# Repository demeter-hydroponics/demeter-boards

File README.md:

# demeter-boards
This is where all the EE related files will go into

All the board data has been stored in these files. Updates will be made and pushed with commit messages
Calculations and other documents will remain on OneDrive

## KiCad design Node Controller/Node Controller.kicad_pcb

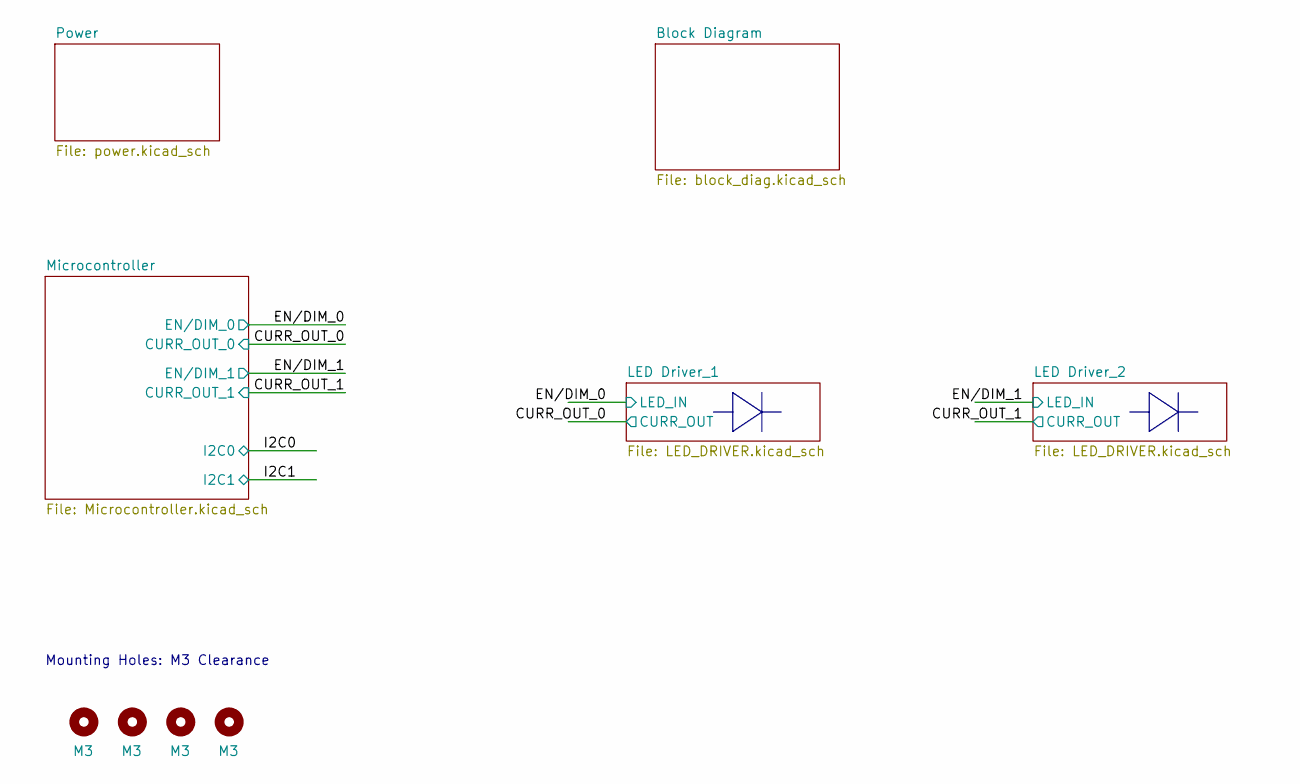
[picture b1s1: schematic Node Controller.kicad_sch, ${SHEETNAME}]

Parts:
H1, H2, H3, H4: M3; MountingHole_3.2mm_M3

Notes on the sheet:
Mounting Holes: M3 Clearance

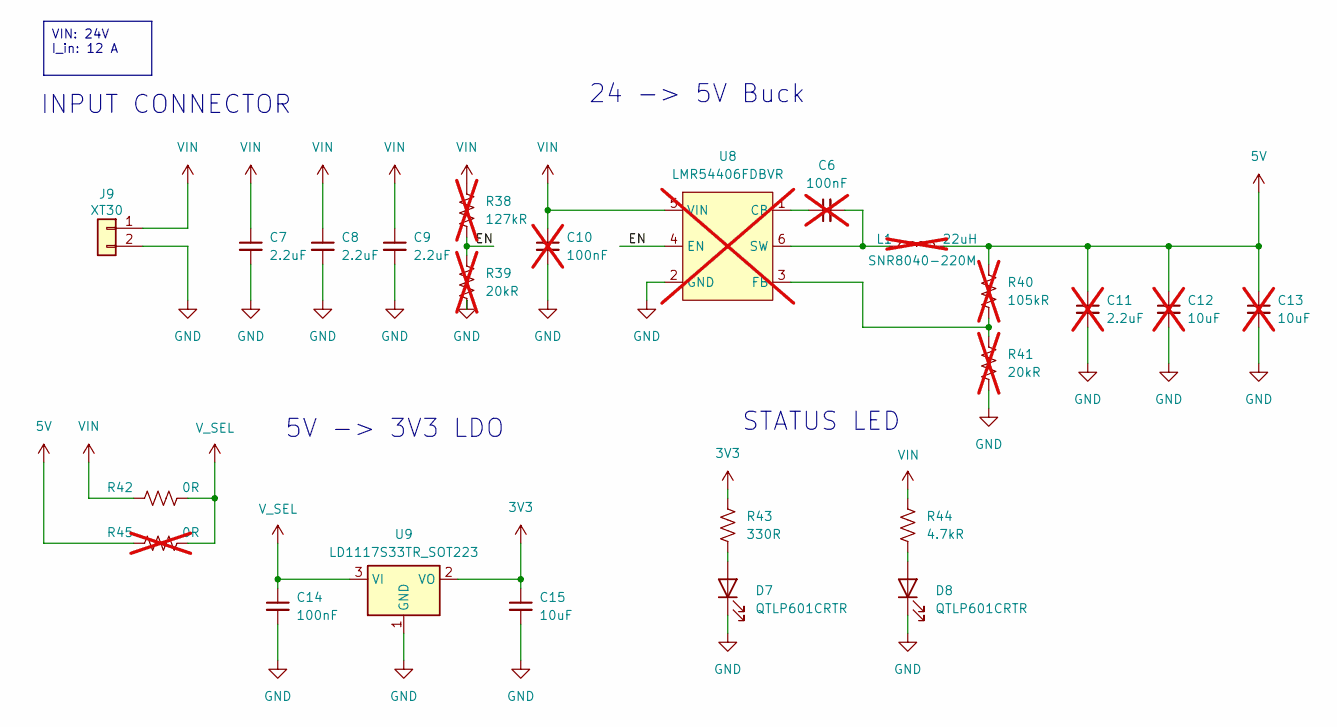
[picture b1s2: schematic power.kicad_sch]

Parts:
C6, C10: 100nF; C_1206_3216Metric; Part Number CL31B104KCFNNNE; not fitted
C7, C8, C9: 2.2uF; C_1206_3216Metric; Part Number CL31B225KCHSNNE
C11: 2.2uF; C_1206_3216Metric; Part Number CL31B225KCHSNNE; not fitted
C12, C13: 10uF; C_1210_3225Metric; Part Number CL32B106KMVNNWE; not fitted
C14: 100nF; C_1206_3216Metric; Part Number CL31B104KCFNNNE
C15: 10uF; C_1210_3225Metric; Part Number CL32B106KMVNNWE
D7, D8: QTLP601CRTR; LED_0603_1608Metric; Part Number QTLP601CRTR
J9: XT30; Part Number XT30
L1: 22uH; L_Bourns-SRN8040_8x8.15mm; Part Number SNR8040-220M; not fitted
R38: 127kR; R_0402_1005Metric; Part Number RC0603FR-07127KL; not fitted
R39, R41: 20kR; R_0402_1005Metric; Part Number RC0603FR-0720KL; not fitted
R40: 105kR; R_0402_1005Metric; Part Number RC0603FR-07105KL; not fitted
R42: 0R; R_0603_1608Metric; Part Number RC0603FR-070RL
R43: 330R; R_0402_1005Metric; Part Number RC0603FR-07330RL
R44: 4.7kR; R_0603_1608Metric; Part Number RC0603FR-074K7L
R45: 0R; R_0603_1608Metric; Part Number RC0603FR-070RL; not fitted
U8: LMR54406FDBVR; SOT-23-6; Part Number LMR54406FDBVR; not fitted
U9: LD1117S33TR_SOT223; SOT-223-3_TabPin2; Part Number LD1117S33TR_SOT223

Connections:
3V3: C15.1, R43.2, U9.2 (VO); also elsewhere on the board
5V: C11.1, C12.1, C13.1, L1.2, R40.1, R45.1; also elsewhere on the board
/Power/EN: R38.2, R39.1, U8.4 (EN)
GND: C7.2, C8.2, C9.2, C10.2, C11.2, C12.2, C13.2, C14.2, C15.2, D7.1 (K), D8.1 (K), J9.2, R39.2, R41.2, U8.2 (GND), U9.1 (GND); also elsewhere on the board
unnamed: D7.2 (A), R43.1
unnamed: D8.2 (A), R44.1
unnamed: C6.1, U8.1 (CB)
unnamed: R40.2, R41.1, U8.3 (FB)
unnamed: C6.2, L1.1, U8.6 (SW)
VIN: C7.1, C8.1, C9.1, C10.1, J9.1, R38.1, R42.1, R44.2, U8.5 (VIN)
V_SEL: C14.1, R42.2, R45.2, U9.3 (VI)

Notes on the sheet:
VIN: 24V I_in: 12 A
5V -> 3V3 LDO
STATUS LED
24 -> 5V Buck
INPUT CONNECTOR

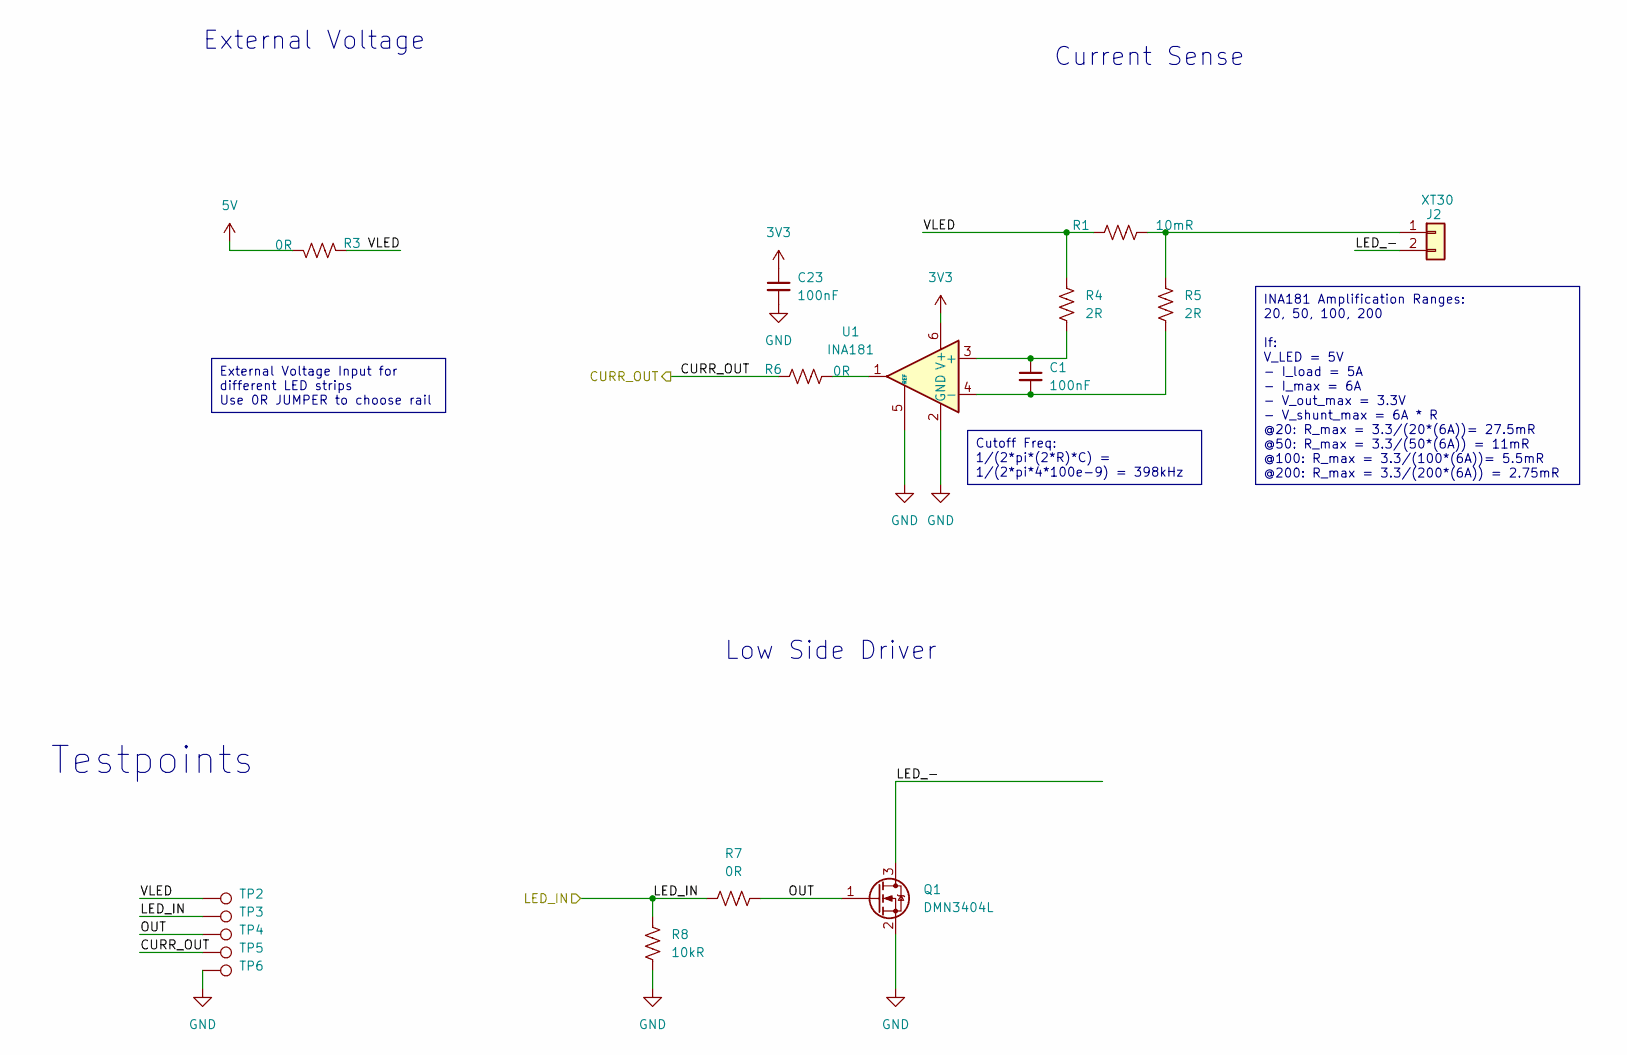
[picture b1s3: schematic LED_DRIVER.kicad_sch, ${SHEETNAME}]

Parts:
C1: 100nF; C_0603_1608Metric; Part Number CL31B104KCFNNNE
C23: 100nF; C_1206_3216Metric; Part Number CL31B104KCFNNNE
J2: XT30; Part Number XT30
Q1: DMN3404L; SOT-23; Part Number DMN3404L
R1: 10mR; R_0805_2012Metric; Part Number PA0805FRF870R01L
R3, R6, R7: 0R; R_0603_1608Metric; Part Number RC0603FR-070RL
R4, R5: 2R; R_0402_1005Metric; Part Number RC0402FR-072RL
R8: 10kR; R_0603_1608Metric; Part Number RC0603FR-0710KL
TP2, TP3, TP4, TP5, TP6: TestPoint_Pad_D1.0mm
U1: INA181; SOT-23-6; Part Number INA181A3IDBV

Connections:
3V3: C23.1, U1.6 (V+); also elsewhere on the board
5V: R3.1; also elsewhere on the board
/CURR_OUT_0: R6.2, TP5.1; also elsewhere on the board
/EN/DIM_0: R7.1, R8.2, TP3.1; also elsewhere on the board
/LED Driver_1/LED_-: J2.2, Q1.3 (D)
/LED Driver_1/OUT: Q1.1 (G), R7.2, TP4.1
/LED Driver_1/VLED: R1.1, R3.2, R4.2, TP2.1
GND: C23.2, Q1.2 (S), R8.1, TP6.1, U1.2 (GND), U1.5 (REF); also elsewhere on the board
unnamed: J2.1, R1.2, R5.2
unnamed: R6.1, U1.1
unnamed: C1.1, R4.1, U1.3 (+)
unnamed: C1.2, R5.1, U1.4 (-)

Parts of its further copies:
C5: 100nF; C_0603_1608Metric; Part Number CL31B104KCFNNNE
C24: 100nF; C_1206_3216Metric; Part Number CL31B104KCFNNNE
J8: XT30; Part Number XT30
Q7: DMN3404L; SOT-23; Part Number DMN3404L
R29: 10mR; R_0805_2012Metric; Part Number PA0805FRF870R01L
R31, R34, R35: 0R; R_0603_1608Metric; Part Number RC0603FR-070RL
R32, R33: 2R; R_0402_1005Metric; Part Number RC0402FR-072RL
R36: 10kR; R_0603_1608Metric; Part Number RC0603FR-0710KL
TP20, TP21, TP22, TP23, TP24: TestPoint_Pad_D1.0mm
U6: INA181; SOT-23-6; Part Number INA181A3IDBV

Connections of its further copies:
3V3: C24.1, U6.6 (V+); also elsewhere on the board
5V: R31.1; also elsewhere on the board
/CURR_OUT_1: R34.2, TP23.1; also elsewhere on the board
/EN/DIM_1: R35.1, R36.2, TP21.1; also elsewhere on the board
/LED Driver_2/LED_-: J8.2, Q7.3 (D)
/LED Driver_2/OUT: Q7.1 (G), R35.2, TP22.1
/LED Driver_2/VLED: R29.1, R31.2, R32.2, TP20.1
GND: C24.2, Q7.2 (S), R36.1, TP24.1, U6.2 (GND), U6.5 (REF); also elsewhere on the board
unnamed: J8.1, R29.2, R33.2
unnamed: R34.1, U6.1
unnamed: C5.1, R32.1, U6.3 (+)
unnamed: C5.2, R33.1, U6.4 (-)

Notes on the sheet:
Cutoff Freq: 1/(2*pi*(2*R)*C) = 1/(2*pi*4*100e-9) = 398kHz
INA181 Amplification Ranges: 20, 50, 100, 200 If: V_LED = 5V - I_load = 5A - I_max = 6A - V_out_max = 3.3V - V_shunt_max = 6A * R @20: R_max = 3.3/(20*(6A))= 27.5mR @50: R_max = 3.3/(50*(6A)) = 11mR @100: R_max = 3.3/(100*(6A))= 5.5mR @200: R_max = 3.3/(200*(6A)) = 2.75mR
External Voltage Input for different LED strips Use 0R JUMPER to choose rail
External Voltage
Testpoints
Low Side Driver
Current Sense

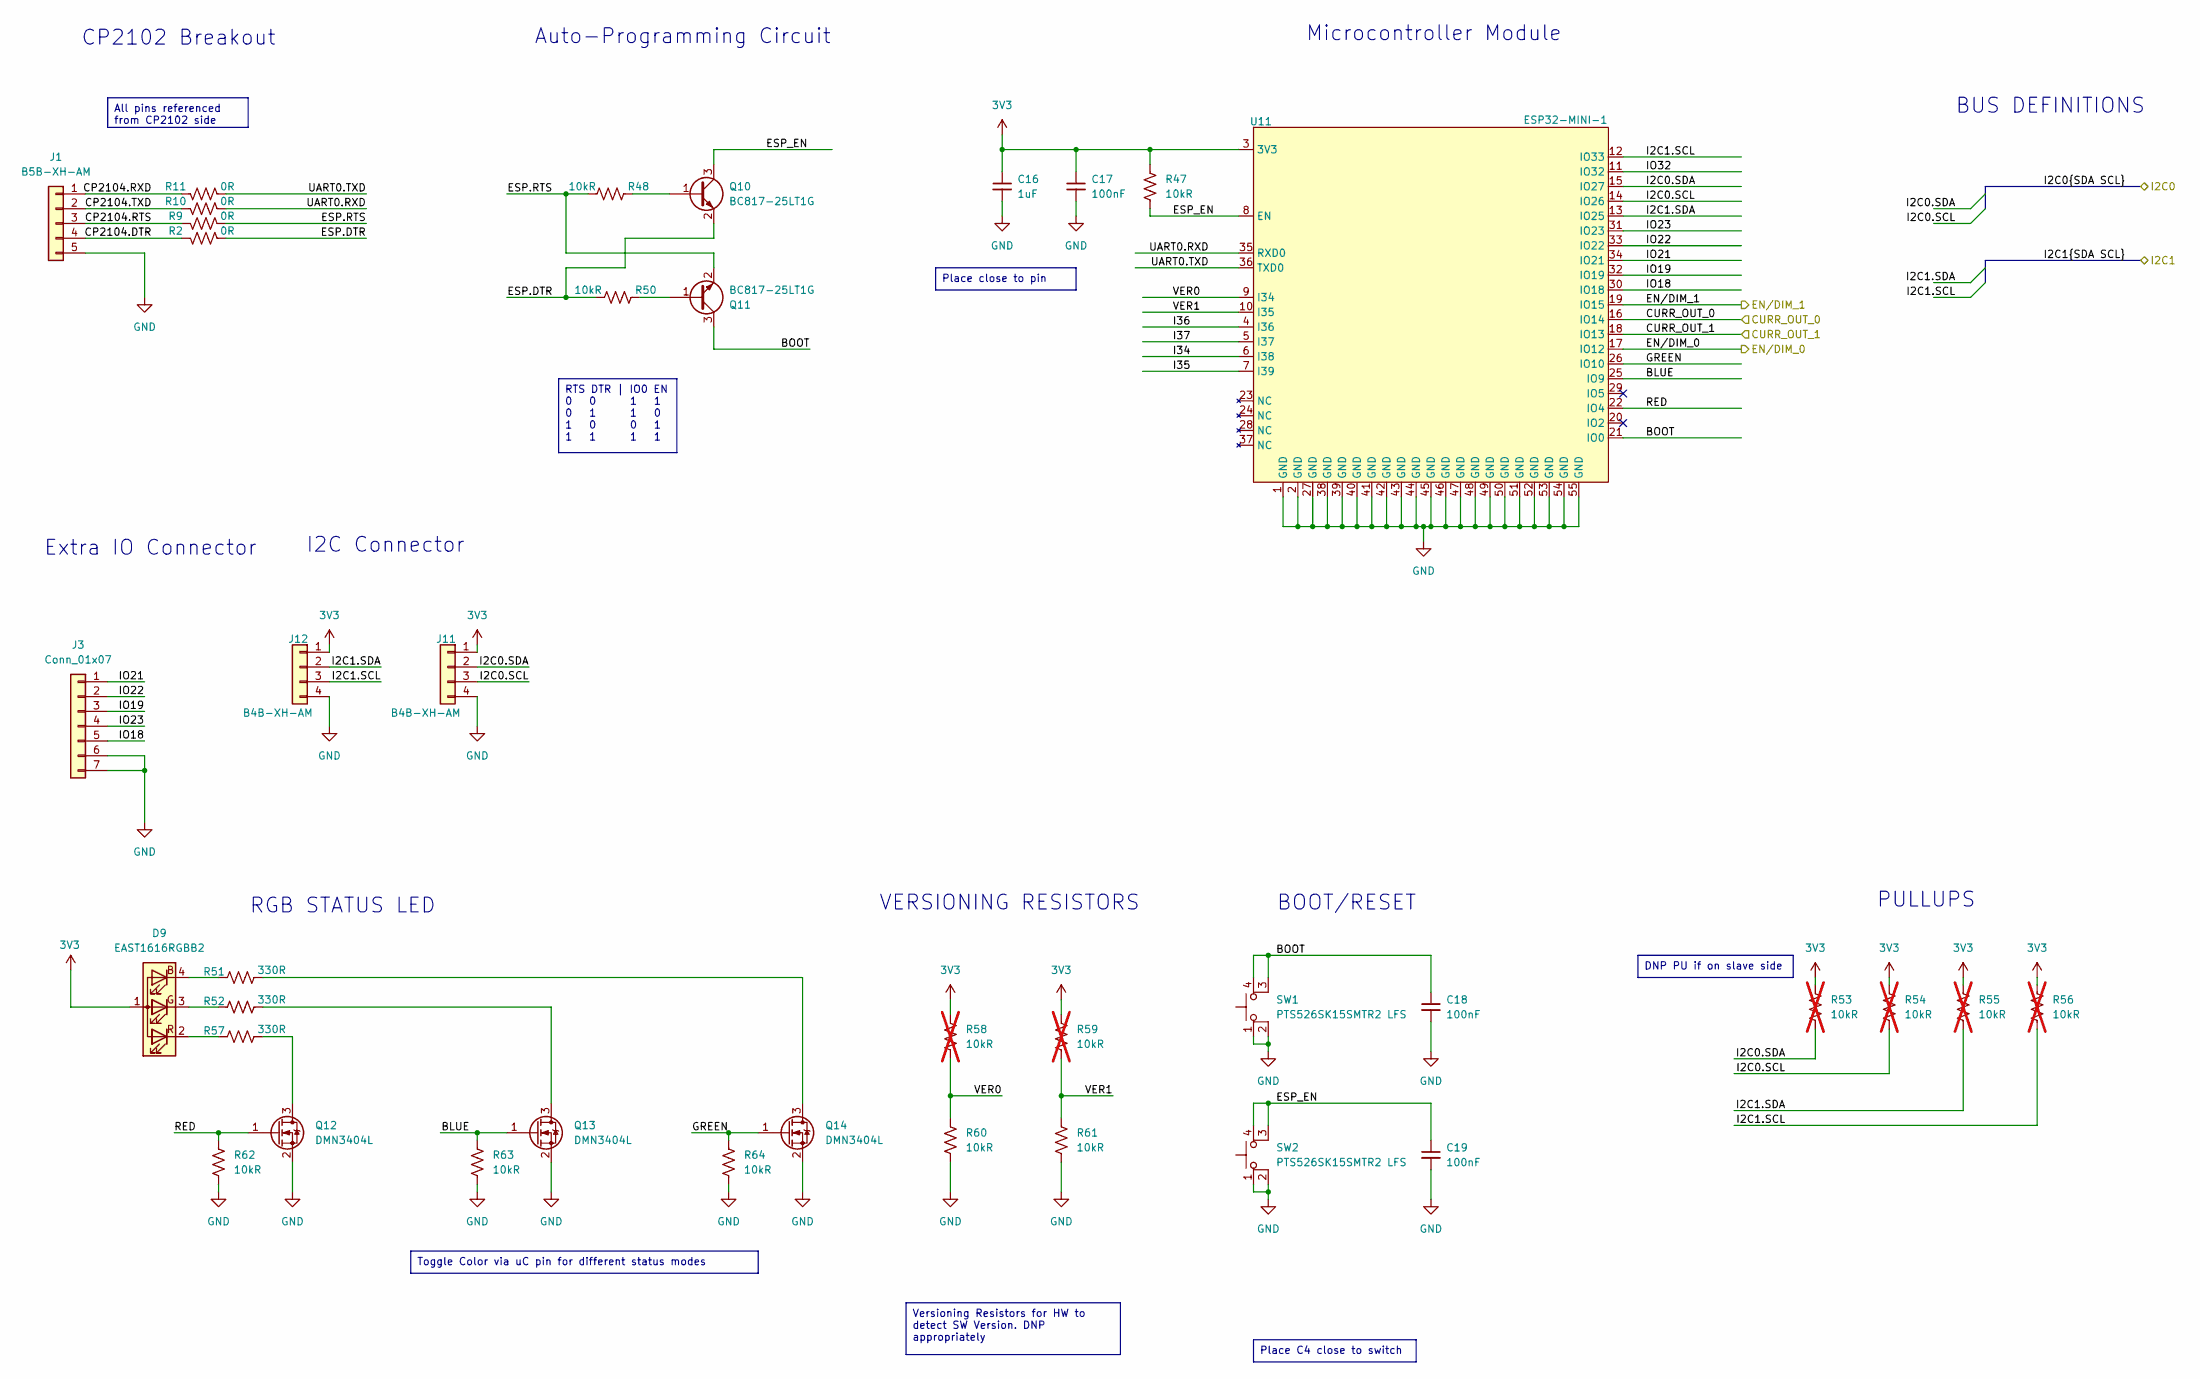
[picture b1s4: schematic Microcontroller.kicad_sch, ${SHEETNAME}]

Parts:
C16: 1uF; C_1206_3216Metric; Part Number CL31B105KCHNNNE
C17, C18, C19: 100nF; C_1206_3216Metric; Part Number CL31B104KCFNNNE
D9: EAST1616RGBB2; Part Number EAST1616RGBB2
J1: B5B-XH-AM; JST_XH_B5B-XH-AM_1x05_P2.50mm_Vertical
J3: Conn_01x07; PinSocket_1x07_P2.54mm_Vertical
J11, J12: B4B-XH-AM; JST_XH_B4B-XH-AM_1x04_P2.50mm_Vertical; Part Number B4B-XH-AM
Q10, Q11: BC817-25LT1G; SOT-23; Part Number BC817-25LT1G
Q12, Q13, Q14: DMN3404L; SOT-23; Part Number DMN3404L
R2, R9, R10, R11: 0R; R_0603_1608Metric; Part Number RC0603FR-070RL
R47, R48, R50, R60, R61, R62, R63, R64: 10kR; R_0603_1608Metric; Part Number RC0603FR-0710KL
R51, R52, R57: 330R; R_0402_1005Metric; Part Number RC0603FR-07330RL
R53, R54, R55, R56, R58, R59: 10kR; R_0603_1608Metric; Part Number RC0603FR-0710KL; not fitted
SW1, SW2: PTS526SK15SMTR2 LFS; Part Number PTS526SK15SMTR2 LFS
U11: ESP32-MINI-1

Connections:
3V3: C16.1, C17.1, D9.1 (A), J11.1, J12.1, R47.1, R53.1, R54.1, R55.1, R56.1, R58.1, R59.1, U11.3 (3V3); also elsewhere on the board
/CURR_OUT_0: U11.16 (IO14); also elsewhere on the board
/CURR_OUT_1: U11.18 (IO13); also elsewhere on the board
/EN/DIM_0: U11.17 (IO12); also elsewhere on the board
/EN/DIM_1: U11.19 (IO15); also elsewhere on the board
/Microcontroller/BLUE: Q13.1 (G), R63.1, U11.25 (IO9)
/Microcontroller/BOOT: C18.1, Q11.3 (C), SW1.3 (K), SW1.4 (A), U11.21 (IO0)
/Microcontroller/CP2104.DTR: J1.4, R2.2
/Microcontroller/CP2104.RTS: J1.3, R9.2
/Microcontroller/CP2104.RXD: J1.1, R11.2
/Microcontroller/CP2104.TXD: J1.2, R10.2
/Microcontroller/ESP.DTR: Q10.2 (E), R2.1, R50.1
/Microcontroller/ESP.RTS: Q11.2 (E), R9.1, R48.1
/Microcontroller/ESP_EN: C19.1, Q10.3 (C), R47.2, SW2.3 (K), SW2.4 (A), U11.8 (EN)
/Microcontroller/GREEN: Q14.1 (G), R64.1, U11.26 (IO10)
/Microcontroller/I2C0.SCL: J11.3, R54.2, U11.14 (IO26)
/Microcontroller/I2C0.SDA: J11.2, R53.2, U11.15 (IO27)
/Microcontroller/I2C1.SCL: J12.3, R56.2, U11.12 (IO33)
/Microcontroller/I2C1.SDA: J12.2, R55.2, U11.13 (IO25)
/Microcontroller/I34: U11.6 (I38)
/Microcontroller/I35: U11.7 (I39)
/Microcontroller/I36: U11.4 (I36)
/Microcontroller/I37: U11.5 (I37)
/Microcontroller/IO18: J3.5, U11.30 (IO18)
/Microcontroller/IO19: J3.3, U11.32 (IO19)
/Microcontroller/IO21: J3.1, U11.34 (IO21)
/Microcontroller/IO22: J3.2, U11.33 (IO22)
/Microcontroller/IO23: J3.4, U11.31 (IO23)
/Microcontroller/IO32: U11.11 (IO32)
/Microcontroller/RED: Q12.1 (G), R62.1, U11.22 (IO4)
/Microcontroller/UART0.RXD: R10.1, U11.35 (RXD0)
/Microcontroller/UART0.TXD: R11.1, U11.36 (TXD0)
/Microcontroller/VER0: R58.2, R60.1, U11.9 (I34)
/Microcontroller/VER1: R59.2, R61.1, U11.10 (I35)
GND: C16.2, C17.2, C18.2, C19.2, J1.5, J3.6, J3.7, J11.4, J12.4, Q12.2 (S), Q13.2 (S), Q14.2 (S), R60.2, R61.2, R62.2, R63.2, R64.2, SW1.1, SW1.2, SW2.1, SW2.2, U11.1 (GND), U11.2 (GND), U11.27 (GND), U11.38 (GND), U11.39 (GND), U11.40 (GND), U11.41 (GND), U11.42 (GND), U11.43 (GND), U11.44 (GND), U11.45 (GND), U11.46 (GND), U11.47 (GND), U11.48 (GND), U11.49 (GND), U11.50 (GND), U11.51 (GND), U11.52 (GND), U11.53 (GND), U11.54 (GND), U11.55 (GND); also elsewhere on the board
unnamed: D9.4 (BK), R51.1
unnamed: D9.3 (GK), R52.1
unnamed: D9.2 (RK), R57.1
unnamed: Q10.1 (B), R48.2
unnamed: Q11.1 (B), R50.2
unnamed: Q12.3 (D), R57.2
unnamed: Q13.3 (D), R52.2
unnamed: Q14.3 (D), R51.2

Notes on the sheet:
Place close to pin
Place C4 close to switch
Versioning Resistors for HW to detect SW Version. DNP appropriately
All pins referenced from CP2102 side
RTS DTR | IO0 EN 0 0 1 1 0 1 1 0 1 0 0 1 1 1 1 1
DNP PU if on slave side
Toggle Color via uC pin for different status modes
Auto-Programming Circuit
I2C Connector
CP2102 Breakout
Extra IO Connector
RGB STATUS LED
VERSIONING RESISTORS
Microcontroller Module
BOOT/RESET
PULLUPS
BUS DEFINITIONS

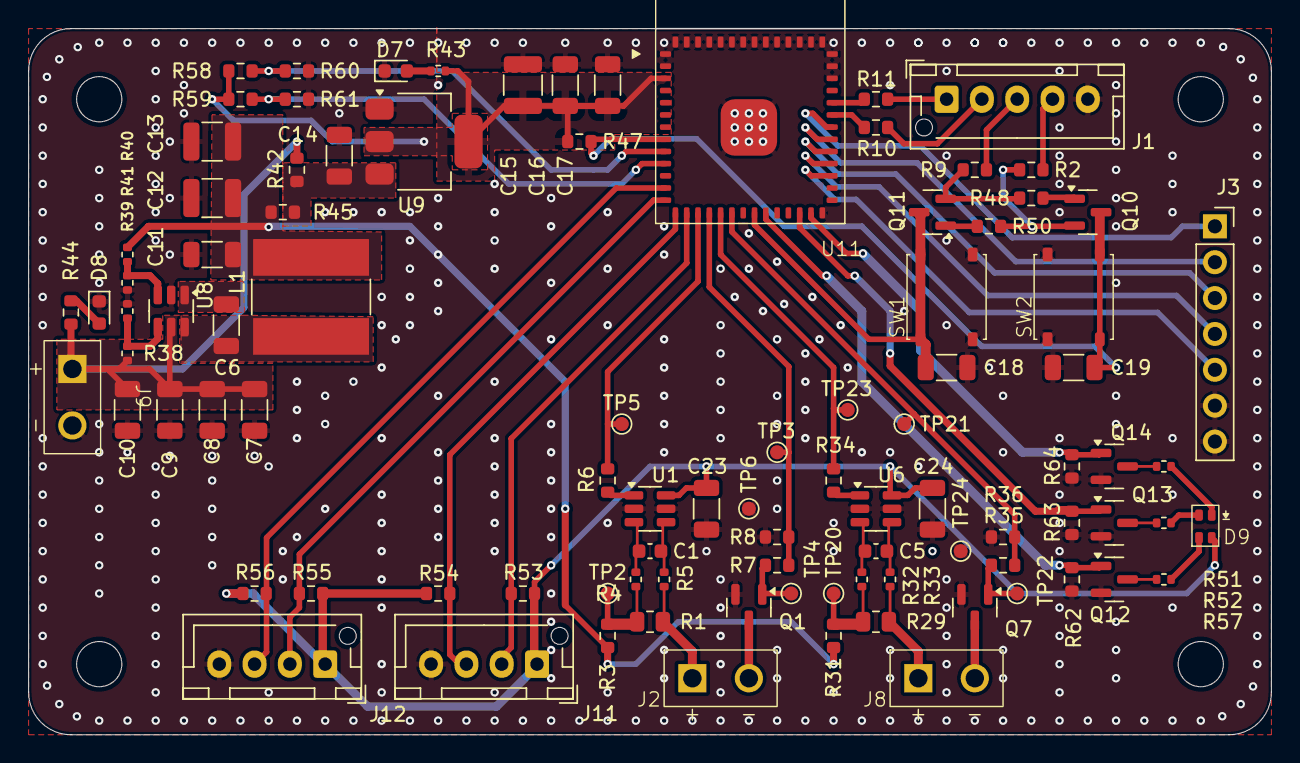
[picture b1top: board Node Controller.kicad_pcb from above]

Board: 4 copper layers, 88.0 x 50.0 mm, 100 parts (0 on the bottom side), 61 nets.

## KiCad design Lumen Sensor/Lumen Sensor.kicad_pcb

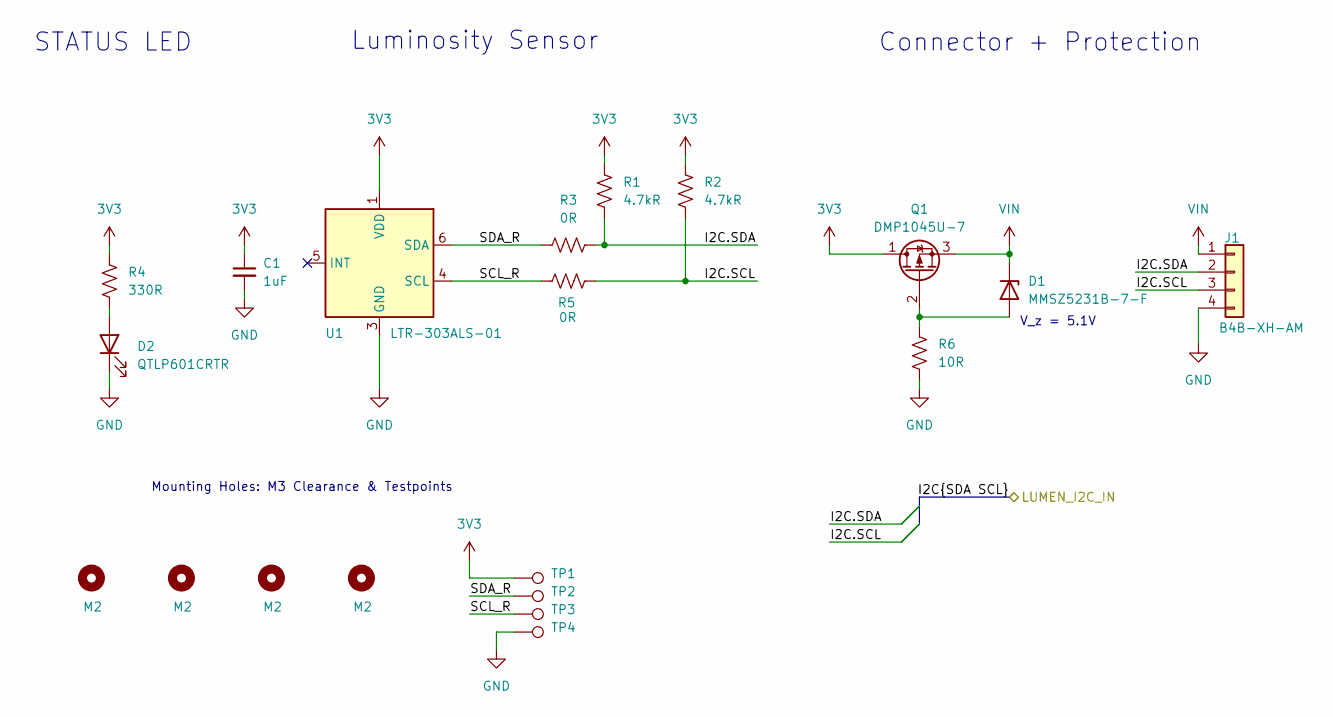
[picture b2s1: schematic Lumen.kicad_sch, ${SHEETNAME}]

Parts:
C1: 1uF; C_1206_3216Metric; Part Number CL31B105KCHNNNE
D1: MMSZ5231B-7-F; D_SOD-123; Part Number MMSZ5231B-7-F
D2: QTLP601CRTR; LED_0603_1608Metric; Part Number QTLP601CRTR
H1, H2, H3, H4: M2; MountingHole_2.2mm_M2_Pad
J1: B4B-XH-AM; JST_XH_B4B-XH-AM_1x04_P2.50mm_Vertical; Part Number B4B-XH-AM
Q1: DMP1045U-7; SOT-23-3; Part Number DMP1045U-7
R1, R2: 4.7kR; R_0603_1608Metric; Part Number RC0603FR-074K7L
R3, R5: 0R; R_0603_1608Metric; Part Number RC0603FR-070RL
R4: 330R; R_0402_1005Metric; Part Number RC0603FR-07330RL
R6: 10R; R_0402_1005Metric; Part Number RC0603FR-0710RL
TP1, TP2, TP3, TP4: TestPoint_Pad_D1.0mm
U1: LTR-303ALS-01; Lite-On_LTR-303ALS-01; Part Number LTR-303ALS-01

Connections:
3V3: C1.1, Q1.1 (D), R1.2, R2.2, R4.2, TP1.1, U1.1 (VDD)
/Lumen Board/I2C.SCL: J1.3, R2.1, R5.2
/Lumen Board/I2C.SDA: J1.2, R1.1, R3.2
/Lumen Board/SCL_R: R5.1, TP3.1, U1.4 (SCL)
/Lumen Board/SDA_R: R3.1, TP2.1, U1.6 (SDA)
GND: C1.2, D2.1 (K), J1.4, R6.2, TP4.1, U1.3 (GND)
unnamed: D1.2 (A), Q1.2 (G), R6.1
unnamed: D2.2 (A), R4.1
VIN: D1.1 (K), J1.1, Q1.3 (S)

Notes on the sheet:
Connector + Protection
V_z = 5.1V
STATUS LED
Luminosity Sensor
Mounting Holes: M3 Clearance & Testpoints

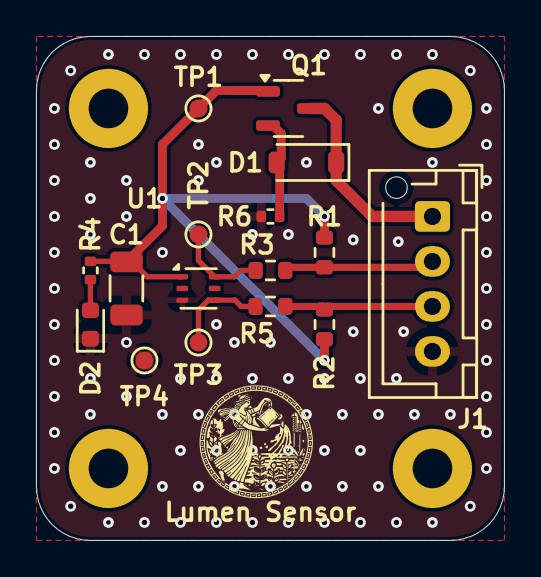
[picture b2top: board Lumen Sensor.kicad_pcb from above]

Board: 4 copper layers, 26.0 x 28.0 mm, 20 parts (0 on the bottom side), 9 nets.

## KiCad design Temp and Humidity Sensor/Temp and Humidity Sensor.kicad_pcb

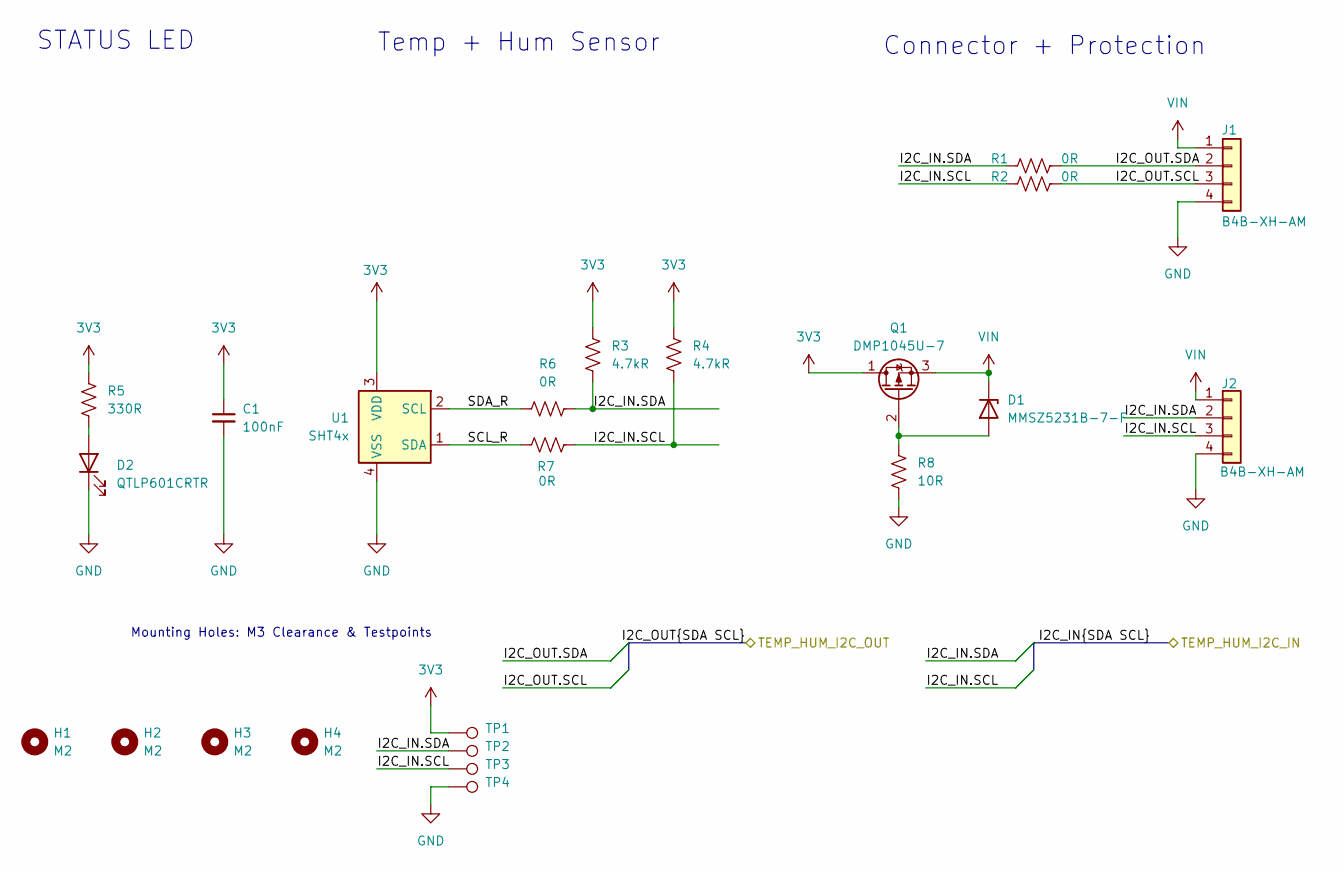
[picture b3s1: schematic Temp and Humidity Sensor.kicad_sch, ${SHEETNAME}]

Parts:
C1: 100nF; C_1206_3216Metric; Part Number CL31B104KCFNNNE
D1: MMSZ5231B-7-F; D_SOD-123; Part Number MMSZ5231B-7-F
D2: QTLP601CRTR; LED_0603_1608Metric; Part Number QTLP601CRTR
H1, H2, H3, H4: M2; MountingHole_2.2mm_M2_Pad
J1, J2: B4B-XH-AM; JST_XH_B4B-XH-AM_1x04_P2.50mm_Vertical; Part Number B4B-XH-AM
Q1: DMP1045U-7; SOT-23-3; Part Number DMP1045U-7
R1, R2, R6, R7: 0R; R_0603_1608Metric; Part Number RC0603FR-070RL
R3, R4: 4.7kR; R_0603_1608Metric; Part Number RC0603FR-074K7L
R5: 330R; R_0402_1005Metric; Part Number RC0603FR-07330RL
R8: 10R; R_0402_1005Metric; Part Number RC0603FR-0710RL
TP1, TP2, TP3, TP4: TestPoint_Pad_D1.0mm
U1: SHT4x; Sensirion_DFN-4_1.5x1.5mm_P0.8mm_SHT4x_NoCentralPad; Part Number SHT40-AD1B

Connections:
3V3: C1.1, Q1.1 (D), R3.2, R4.2, R5.2, TP1.1, U1.3 (VDD)
/I2C_IN.SCL: J2.3, R2.1, R4.1, R7.2, TP3.1
/I2C_IN.SDA: J2.2, R1.1, R3.1, R6.2, TP2.1
/I2C_OUT.SCL: J1.3, R2.2
/I2C_OUT.SDA: J1.2, R1.2
/SCL_R: R7.1, U1.1 (SDA)
/SDA_R: R6.1, U1.2 (SCL)
GND: C1.2, D2.1 (K), J1.4, J2.4, R8.2, TP4.1, U1.4 (VSS)
unnamed: D1.2 (A), Q1.2 (G), R8.1
unnamed: D2.2 (A), R5.1
VIN: D1.1 (K), J1.1, J2.1, Q1.3 (S)

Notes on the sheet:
Connector + Protection
Mounting Holes: M3 Clearance & Testpoints
Temp + Hum Sensor
STATUS LED

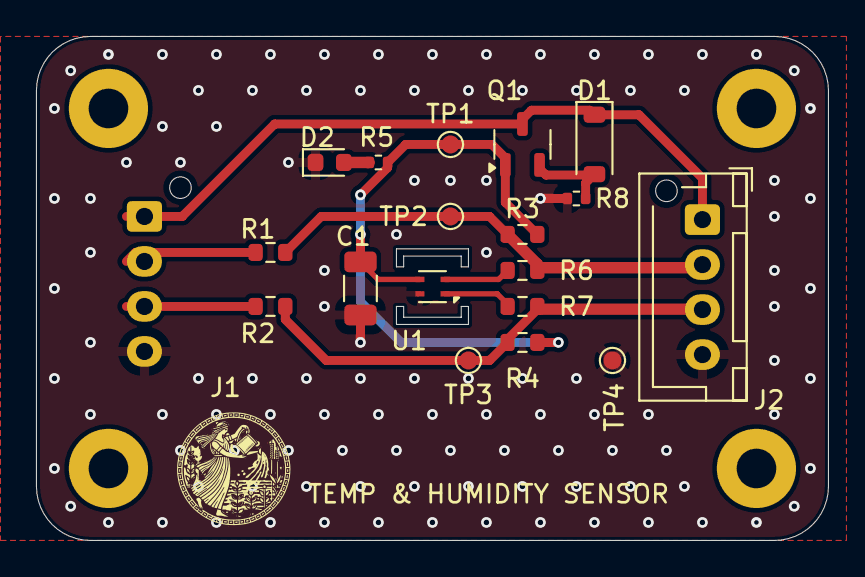
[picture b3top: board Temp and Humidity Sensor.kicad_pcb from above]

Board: 4 copper layers, 44.0 x 28.0 mm, 23 parts (1 on the bottom side), 11 nets.

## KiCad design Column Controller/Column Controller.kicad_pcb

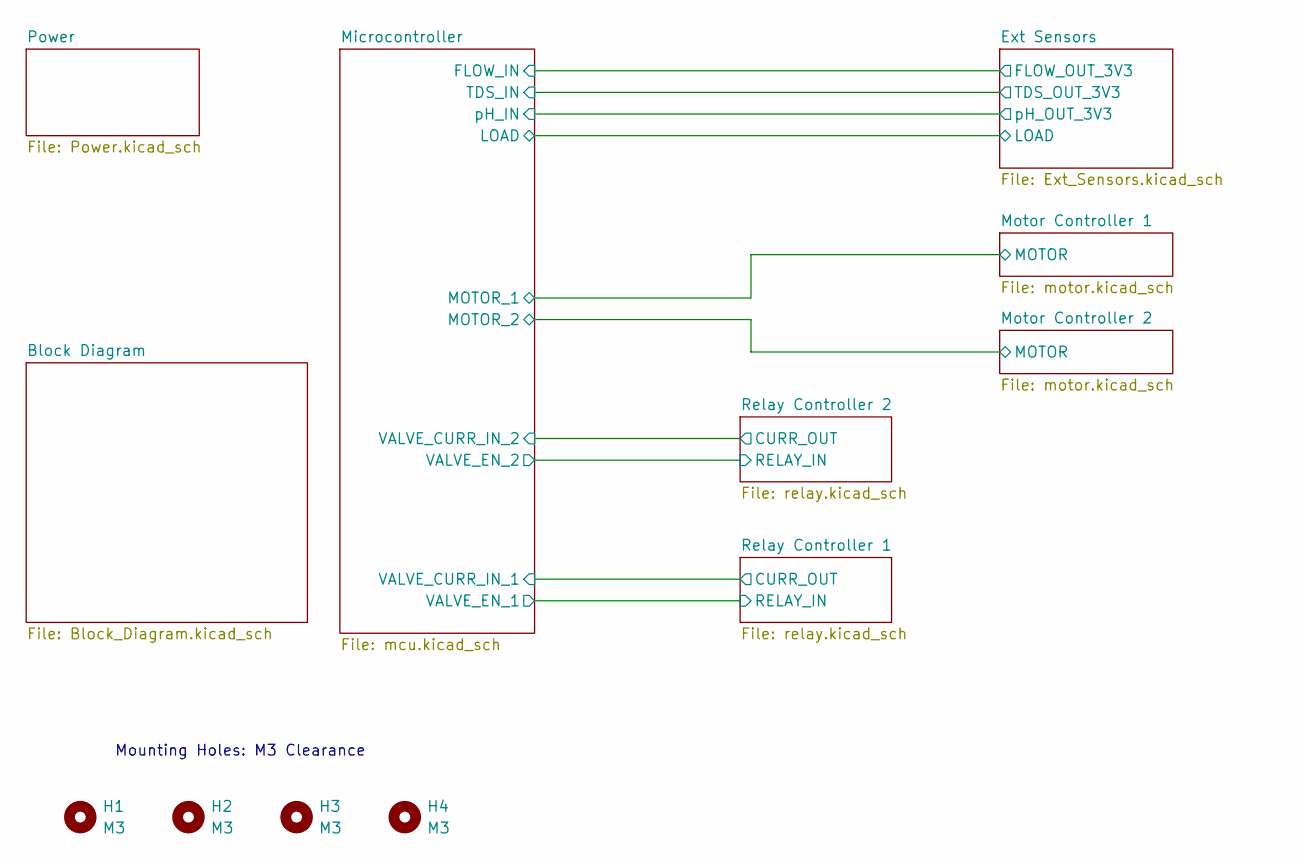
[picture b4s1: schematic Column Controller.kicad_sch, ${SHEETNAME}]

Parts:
H1, H2, H3, H4: M3; MountingHole_3.2mm_M3

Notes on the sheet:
Mounting Holes: M3 Clearance

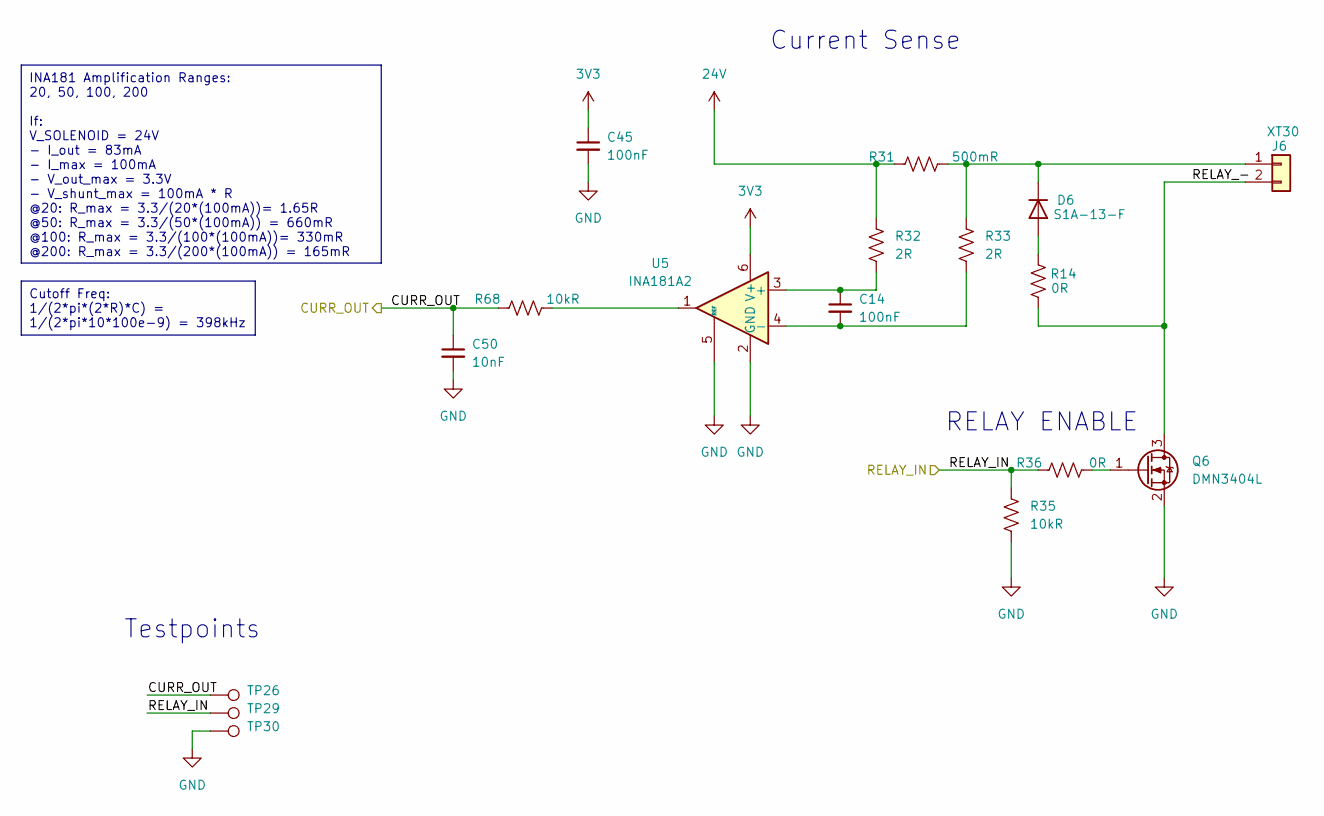
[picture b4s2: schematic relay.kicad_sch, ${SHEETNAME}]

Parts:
C14, C45: 100nF; C_0402_1005Metric; Part Number CL31B104KCFNNNE
C50: 10nF; C_0402_1005Metric; Part Number CL05B103KO5NNNC
D6: S1A-13-F; D_SMA
J6: XT30
Q6: DMN3404L; SOT-23; Part Number DMN3404L
R14, R36: 0R; R_0603_1608Metric; Part Number RC0603FR-070RL
R31: 500mR; R_0603_1608Metric; Part Number RL0603FR-070R5L
R32, R33: 2R; R_0402_1005Metric; Part Number RC0402FR-072RL
R35, R68: 10kR; R_0603_1608Metric; Part Number RC0603FR-0710KL
TP26, TP29, TP30: TestPoint_Pad_D1.0mm
U5: INA181A2; SOT-23-6; Part Number INA181A2IDVB

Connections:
3V3: C45.1, U5.6 (V+); also elsewhere on the board
24V: R31.1, R32.2; also elsewhere on the board
/Relay Controller 1/CURR_OUT: C50.1, R68.1, TP26.1; also elsewhere on the board
/Relay Controller 1/RELAY_-: J6.2, Q6.3 (D), R14.2
/Relay Controller 1/RELAY_IN: R35.2, R36.2, TP29.1; also elsewhere on the board
GND: C45.2, C50.2, Q6.2 (S), R35.1, TP30.1, U5.2 (GND), U5.5 (REF); also elsewhere on the board
unnamed: Q6.1 (G), R36.1
unnamed: R68.2, U5.1
unnamed: C14.1, R32.1, U5.3 (+)
unnamed: C14.2, R33.1, U5.4 (-)

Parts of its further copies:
C33, C47: 100nF; C_0402_1005Metric; Part Number CL31B104KCFNNNE
C51: 10nF; C_0402_1005Metric; Part Number CL05B103KO5NNNC
D4: S1A-13-F; D_SMA
J10: XT30
Q9: DMN3404L; SOT-23; Part Number DMN3404L
R16, R66: 0R; R_0603_1608Metric; Part Number RC0603FR-070RL
R62: 500mR; R_0603_1608Metric; Part Number RL0603FR-070R5L
R63, R64: 2R; R_0402_1005Metric; Part Number RC0402FR-072RL
R67, R69: 10kR; R_0603_1608Metric; Part Number RC0603FR-0710KL
TP27, TP34, TP35: TestPoint_Pad_D1.0mm
U11: INA181A2; SOT-23-6; Part Number INA181A2IDVB

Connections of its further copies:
3V3: C47.1, U11.6 (V+); also elsewhere on the board
24V: R62.1, R63.2; also elsewhere on the board
/Relay Controller 2/CURR_OUT: C51.1, R69.1, TP27.1; also elsewhere on the board
/Relay Controller 2/RELAY_-: J10.2, Q9.3 (D), R16.2
/Relay Controller 2/RELAY_IN: R66.2, R67.2, TP34.1; also elsewhere on the board
GND: C47.2, C51.2, Q9.2 (S), R67.1, TP35.1, U11.2 (GND), U11.5 (REF); also elsewhere on the board
unnamed: Q9.1 (G), R66.1
unnamed: R69.2, U11.1
unnamed: C33.1, R63.1, U11.3 (+)
unnamed: C33.2, R64.1, U11.4 (-)

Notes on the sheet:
INA181 Amplification Ranges: 20, 50, 100, 200 If: V_SOLENOID = 24V - I_out = 83mA - I_max = 100mA - V_out_max = 3.3V - V_shunt_max = 100mA * R @20: R_max = 3.3/(20*(100mA))= 1.65R @50: R_max = 3.3/(50*(100mA)) = 660mR @100: R_max = 3.3/(100*(100mA))= 330mR @200: R_max = 3.3/(200*(100mA)) = 165mR
Cutoff Freq: 1/(2*pi*(2*R)*C) = 1/(2*pi*10*100e-9) = 398kHz
Testpoints
Current Sense
RELAY ENABLE
